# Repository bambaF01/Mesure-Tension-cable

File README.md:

# Tutoriel ESP32 - Mesure de forces par Bluetooth

Ce tutoriel explique le fonctionnement de la lecture des capteurs jusqu'a l'affichage et l'enregistrement.
Système complet de mesure et d'affichage de forces utilisant deux ESP32 communiquant via Bluetooth.

##  Description du projet

Ce projet permet de **mesurer 4 forces en temps réel** à l'aide de capteurs HX711, de les **transmettre sans fil via Bluetooth** à un second ESP32 qui les **affiche sur un écran OLED**, et d'**enregistrer les données sur ordinateur** au format CSV.

### Architecture du système

```
[4x Capteurs HX711] → [ESP32 Maître] → Bluetooth → [ESP32 Esclave] → [Écran OLED]
                                                          ↓
                                                    [USB/Série]
                                                          ↓
                                                    [Ordinateur] → [Fichiers CSV]
```

##  Structure du projet

```
Code_ESP32/
├── README.md                        #  Ce fichier
│
├── ESP32_BT_Emetteur/              #  ESP32 MAÎTRE (émetteur)
│   ├── README.md                    #    Documentation du maître
│   └── ESP32_BT_Emetteur.ino       #    Code Arduino pour lecture HX711 + Bluetooth TX
│
├── ESP32_BT_Recepteur_MAC/         #  ESP32 ESCLAVE (récepteur)
│   ├── README.md                    #    Documentation de l'esclave
│   └── ESP32_BT_Recepteur_MAC.ino  #    Code Arduino pour affichage OLED + Bluetooth RX
│
└── Enregistrement_CSV/             #  Enregistrement des données
    ├── README_APPLICATION.md        #    Guide d'utilisation
    ├── enregistrement_serial.py     #    Script Python d'enregistrement
    ├── requirements.txt             #    Dépendances Python
    ├── lecture_USB_ESP32_mac.command     #  Lanceur macOS
    ├── lecture_USB_ESP32_linux.sh        #  Lanceur Linux
    ├── lecture_USB_ESP32_windows.bat     #  Lanceur Windows
    └── donnees_csv/                 #     Dossier des fichiers CSV enregistrés
```

##  Démarrage rapide

### Étape 1 : Préparer le matériel

**ESP32 Maître (Émetteur)** :
- Connecter 4 capteurs HX711 :
  - HX711_1 → GPIO 34
  - HX711_2 → GPIO 35
  - HX711_3 → GPIO 32
  - HX711_4 → GPIO 33
  - CLK (horloge) → GPIO 18
- Bouton de tare → GPIO 13
- Batterie exterieure pour la recharge

**ESP32 Esclave (Récepteur)** :
- Écran OLED :
  - SDA → GPIO 21
  - SCL → GPIO 22
- Bouton pause affichage → GPIO 13
- Connexion USB

### Étape 2 : Flasher les ESP32

1. **Installer Arduino IDE** avec support ESP32
2. **Configurer l'IDE Arduino (support ESP32)** :
   - Ouvrir Arduino IDE > **Fichier** > **Préférences**
   - Dans **URL de gestionnaire de cartes supplémentaires**, ajouter `https://dl.espressif.com/dl/package_esp32_index.json`
   - Ouvrir **Outils** > **Type de carte** > **Gestionnaire de cartes...**
   - Rechercher `esp32` et installer **esp32 by Espressif Systems**
   - Sélectionner **Carte** : ESP32 Dev Module 
   - Sélectionner **Port** : le port USB de l'ESP32
   - Régler **Vitesse** : 115200 bauds

3. **Installer les bibliothèques** :
   - `BluetoothSerial` (inclus avec ESP32)
   - `HX711` (par Bogdan Necula)
   - `Adafruit GFX Library`
   - `Adafruit SSD1306`

4. **Flasher l'ESP32 Esclave d'abord** :
   - Ouvrir `ESP32_BT_Recepteur_MAC/ESP32_BT_Recepteur_MAC.ino`
   - Téléverser vers l'ESP32 esclave
   - Ouvrir le Moniteur Série (115200 bauds)
   - **Noter l'adresse MAC Bluetooth** affichée (ex: `8C:4F:00:63:4A:F6`)

5. **Flasher l'ESP32 Maître** :
   - Ouvrir `ESP32_BT_Emetteur/ESP32_BT_Emetteur.ino`
   - **Modifier ligne 28** : remplacer l'adresse MAC par celle de votre esclave :
     ```cpp
     uint8_t slaveMAC[] = {0x8C, 0x4F, 0x00, 0x63, 0x4A, 0xF6};
     ```
   - Téléverser vers l'ESP32 maître

### Étape 3 : Utiliser le système

1. **Allumer l'ESP32 esclave** (récepteur) en premier
2. **Allumer l'ESP32 maître** (émetteur) en deuxiéme
3. La connexion Bluetooth s'établit automatiquement
4. Les 4 forces s'affichent en temps réel sur l'écran OLED
5. Pour enregistrer les données : voir section suivante

### Étape 4 : Enregistrer les données (optionnel)

1. **Installer Python 3** et les dépendances :
   ```bash
   cd Enregistrement_CSV/
   pip install -r requirements.txt
   ```

2. **Lancer l'enregistrement** :
   - **macOS** : double-cliquer sur `lecture_USB_ESP32_mac.command`
   - **Linux** : double-cliquer sur `lecture_USB_ESP32_linux.sh`
   - **Windows** : double-cliquer sur `lecture_USB_ESP32_windows.bat`

3. Les données sont enregistrées dans `Enregistrement_CSV/donnees_csv/`

##  Fonctionnalités détaillées

### ESP32 Maître (Émetteur)

 **Mesure des forces** :
- Lecture de 4 capteurs HX711 simultanément
- Conversion automatique en Newtons (N)
- Tare automatique au démarrage
- Bouton de tare manuel pendant l'utilisation

 **Communication** :
- Mode Bluetooth Maître
- Connexion automatique à l'esclave via adresse MAC
- Reconnexion automatique en cas de perte de signal
- Envoi des 4 forces au format tabulé

 **Calibration** :
- Facteurs de calibration configurables (lignes 12-15)
- Affichage sur Moniteur Série pour débogage

### ESP32 Esclave (Récepteur)

 **Affichage OLED** :
- Écran 128x64 pixels
- Affichage en temps réel des 4 forces (C1, C2, C3, C4)
- Indicateur d'état Bluetooth
- Interface claire et lisible

 **Communication** :
- Mode Bluetooth Esclave
- Affichage de l'adresse MAC au démarrage
- Attente de connexion du maître
- Réception et parsing des données

 **Contrôle** :
- Bouton pour mettre en pause/reprendre l'affichage
- Gestion des erreurs de parsing
- Détection de déconnexion

### Enregistrement CSV

 **Acquisition** :
- Détection automatique du port USB de l'ESP32
- Connexion automatique à 115200 bauds
- Lecture en temps réel des données série

 **Enregistrement** :
- Création automatique du dossier `donnees_csv/`
- Nom de fichier avec horodatage : `donnees_forces_YYYYMMDD_HHMMSS.csv`
- Format CSV standard avec en-têtes

 **Compatibilité** :
- Scripts de lancement pour macOS, Linux et Windows
- Détection automatique du port série
- Pas de configuration manuelle nécessaire

##  Format des données

### Transmission Bluetooth
```
12.34\t23.45\t34.56\t45.67\n
```
(4 valeurs séparées par tabulations, en Newtons)

### Fichiers CSV
```csv
Force_1_N,Force_2_N,Force_3_N,Force_4_N
12.34,23.45,34.56,45.67
12.35,23.46,34.57,45.68
12.36,23.47,34.59,45.69
...
```

##  Prérequis

### Matériel requis

- **2x ESP32 WROOM-32E** (ou compatible)
- **4x modules HX711** avec capteurs de charge/pression
- **1x écran OLED SSD1306** (128x64 pixels, I2C)
- **2x boutons poussoirs** (avec pull-up)
- **Câbles de connexion** et alimentation

### Logiciels requis

**Pour flasher les ESP32** :
- Arduino IDE 1.8+ ou 2.x
- Support ESP32 (via Board Manager)
- Bibliothèques :
  - `BluetoothSerial` (inclus)
  - `HX711` par Bogdan Necula
  - `Adafruit GFX Library`
  - `Adafruit SSD1306`
  - `esp_bt_device` (inclus)

**Pour enregistrer les données** :
- Python 3.7+
- `pyserial` (dans requirements.txt)

##  Configuration et calibration

### Calibration des capteurs HX711

1. Modifier les facteurs de calibration dans `ESP32_BT_Emetteur.ino` (lignes 12-15) :
   ```cpp
   #define SCALE_FACTOR_1 110.95757
   #define SCALE_FACTOR_2 109.68881
   #define SCALE_FACTOR_3 109.27245
   #define SCALE_FACTOR_4 107.75708
   ```

2. Pour recalibrer un capteur :
   - Placer un poids connu (ex: 1 kg)
   - Lire la valeur brute
   - Calculer : `SCALE_FACTOR = valeur_brute / poids_connu`

### Connexion Bluetooth

L'adresse MAC de l'esclave est affichée au démarrage. Pour la modifier dans le maître :
```cpp
uint8_t slaveMAC[] = {0x8C, 0x4F, 0x00, 0x63, 0x4A, 0xF6};
```

##  Dépannage

### Problème : ESP32 maître ne se connecte pas à l'esclave

**Solutions** :
1. Vérifier que l'adresse MAC est correcte dans le code maître
2. S'assurer que l'esclave est démarré AVANT le maître
3. Vérifier les messages dans le Moniteur Série
4. Redémarrer les deux ESP32

### Problème : Écran OLED n'affiche rien

**Solutions** :
1. Vérifier les connexions I2C (SDA=21, SCL=22)
2. Vérifier l'adresse I2C (0x3C par défaut)
3. Tester avec un scanner I2C
4. Vérifier l'alimentation de l'écran

### Problème : Valeurs de force instables

**Solutions** :
1. Appuyer sur le bouton de tare
2. Vérifier les connexions des HX711
3. Recalibrer les capteurs
4. Vérifier l'alimentation (tensions stables)

### Problème : Port USB non détecté

**Solutions** :
1. Installer les pilotes USB CH340/CP2102
2. Vérifier le câble USB 
3. Redémarrer l'ESP32
4. Spécifier manuellement le port dans le script Python

##  Documentation supplémentaire

Consultez les README dans chaque dossier pour plus de détails :

- **[ESP32_BT_Emetteur/README.md](ESP32_BT_Emetteur/README.md)** - Configuration détaillée du maître
- **[ESP32_BT_Recepteur_MAC/README.md](ESP32_BT_Recepteur_MAC/README.md)** - Configuration détaillée de l'esclave 
- **[Enregistrement_CSV/README_APPLICATION.md](Enregistrement_CSV/README_APPLICATION.md)** - Guide complet d'enregistrement

##  Conseils d'utilisation

-  Utiliser une alimentation stable pour les capteurs HX711
-  Effectuer la tare avant chaque série de mesures
-  Laisser les capteurs se stabiliser quelques secondes
-  Les fichiers CSV sont horodatés, aucun risque d'écrasement
-  Le système fonctionne en continu, pas besoin de réinitialiser

##  Notes techniques

- **Bluetooth SPP** : Utilise le profil Serial Port Profile
- **Fréquence** : ~10 mesures/seconde (délai 100ms)
- **Précision** : 2 décimales pour les forces en Newtons
- **Format** : Tabulations pour la transmission, virgules pour le CSV

---

Profitez de votre système de mesure ESP32 !

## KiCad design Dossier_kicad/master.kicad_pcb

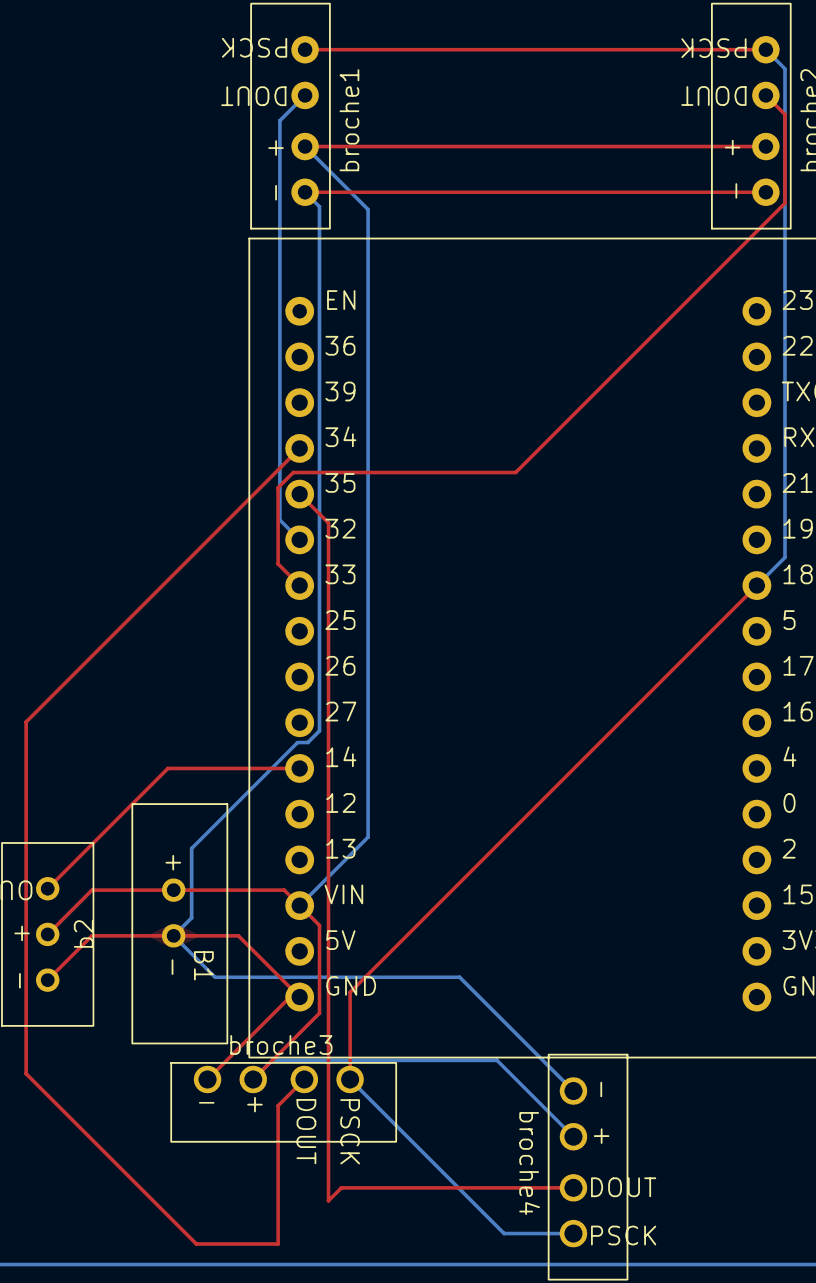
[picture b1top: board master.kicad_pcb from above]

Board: 2 copper layers, 7 parts (0 on the bottom side), 7 nets.

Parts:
B1: broche_double
ESP32-WROOM-32E1: ESP32_DevKit_38pin_v2
b2: broche_tri
broche1, broche2, broche3, broche4: TerminalBlock

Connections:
unnamed: B1.1 (+), b2.2 (VCC), broche1.2 (VCC), broche2.2 (VCC), broche3.2 (VCC), broche4.2 (VCC)
unnamed: B1.2 (-), b2.1 (GND), broche1.1 (GND), broche2.1 (GND), broche3.1 (GND), broche4.1 (GND)
unnamed: ESP32-WROOM-32E1.23 (18), broche1.4 (PSCK), broche2.4 (PSCK), broche3.4 (PSCK), broche4.4 (PSCK)
unnamed: ESP32-WROOM-32E1.6 (32), broche1.3 (DOUT)
unnamed: ESP32-WROOM-32E1.7 (33), broche2.3 (DOUT)
unnamed: ESP32-WROOM-32E1.4 (34), broche3.3 (DOUT)
unnamed: ESP32-WROOM-32E1.5 (35), broche4.3 (DOUT)

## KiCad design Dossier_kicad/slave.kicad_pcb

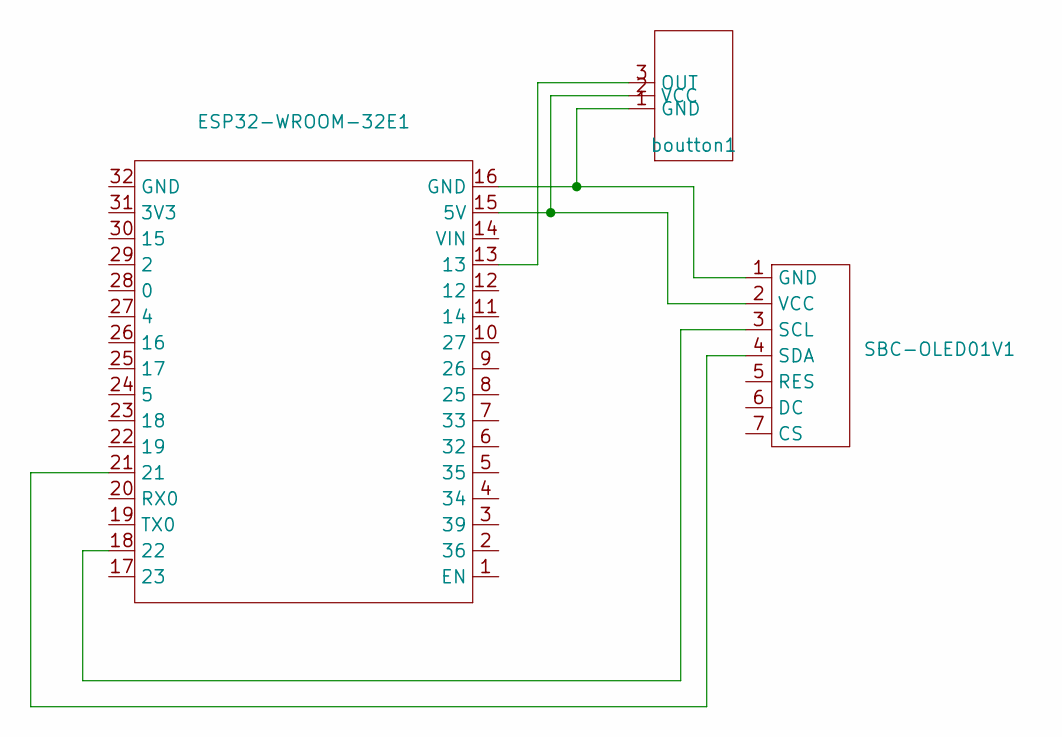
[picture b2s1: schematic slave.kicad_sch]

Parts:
ESP32-WROOM-32E1: ESP32_DevKit_38pin_v2
SBC-OLED01V1: SBC-OLED01V2
boutton1: broche_tri

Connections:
unnamed: ESP32-WROOM-32E1.15 (5V), SBC-OLED01V1.2 (VCC), boutton1.2 (VCC)
unnamed: ESP32-WROOM-32E1.18 (22), SBC-OLED01V1.3 (SCL)
unnamed: ESP32-WROOM-32E1.16 (GND), SBC-OLED01V1.1 (GND), boutton1.1 (GND)
unnamed: ESP32-WROOM-32E1.21, SBC-OLED01V1.4 (SDA)
unnamed: ESP32-WROOM-32E1.13, boutton1.3 (OUT)

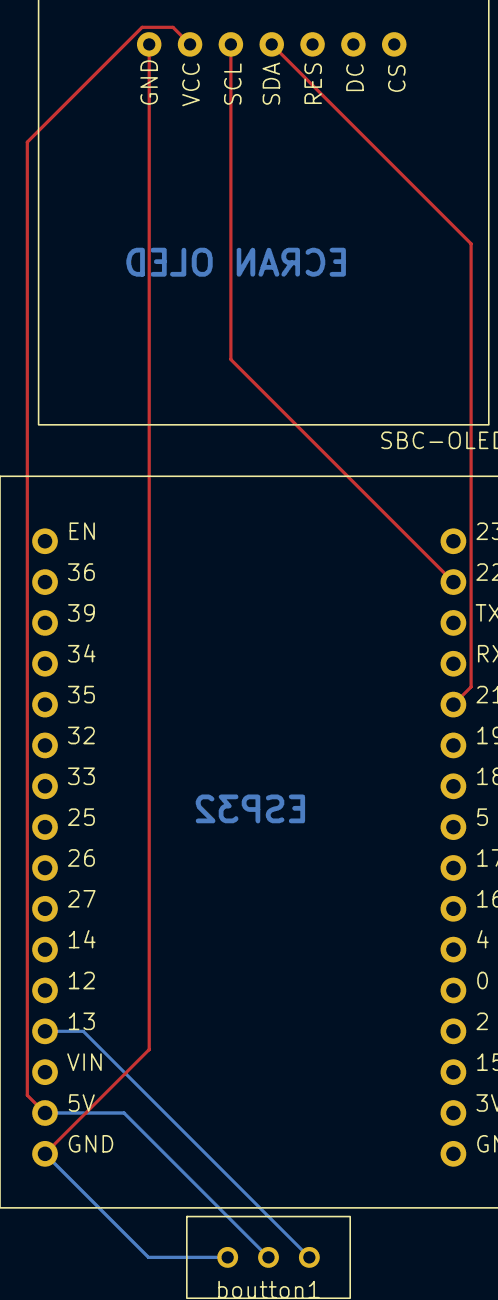
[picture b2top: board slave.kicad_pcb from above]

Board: 2 copper layers, 3 parts (0 on the bottom side), 5 nets.

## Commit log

2026-01-19 Add root README and remove TUTORIEL_ESP32
2026-01-19 Fix schema image paths
2026-01-19 Update force calculation in README
    Removed correction factor for sensor reading in force calculation.
2026-01-19 Remove link to main README from ESP32_BT_Emetteur
    Removed the link to the main README from the ESP32_BT_Emetteur README.
2026-01-19 Remove emojis from README.md headings
2026-01-19 Update README formatting and section titles
2026-01-19 Clean up README formatting and content
    Removed redundant line and adjusted formatting.
2026-01-19 Remove sqrt(2.0) from scale readings
2026-01-19 Clean up architecture diagram in README
    Removed unnecessary HTML entities from the architecture diagram.
2026-01-20 Revise system architecture diagram
    Updated system architecture diagram in README.
2026-02-13 Modifs
2026-03-12 Add KiCad alim project and CSV GUI
2026-03-12 Add Windows exe build and portable data paths
